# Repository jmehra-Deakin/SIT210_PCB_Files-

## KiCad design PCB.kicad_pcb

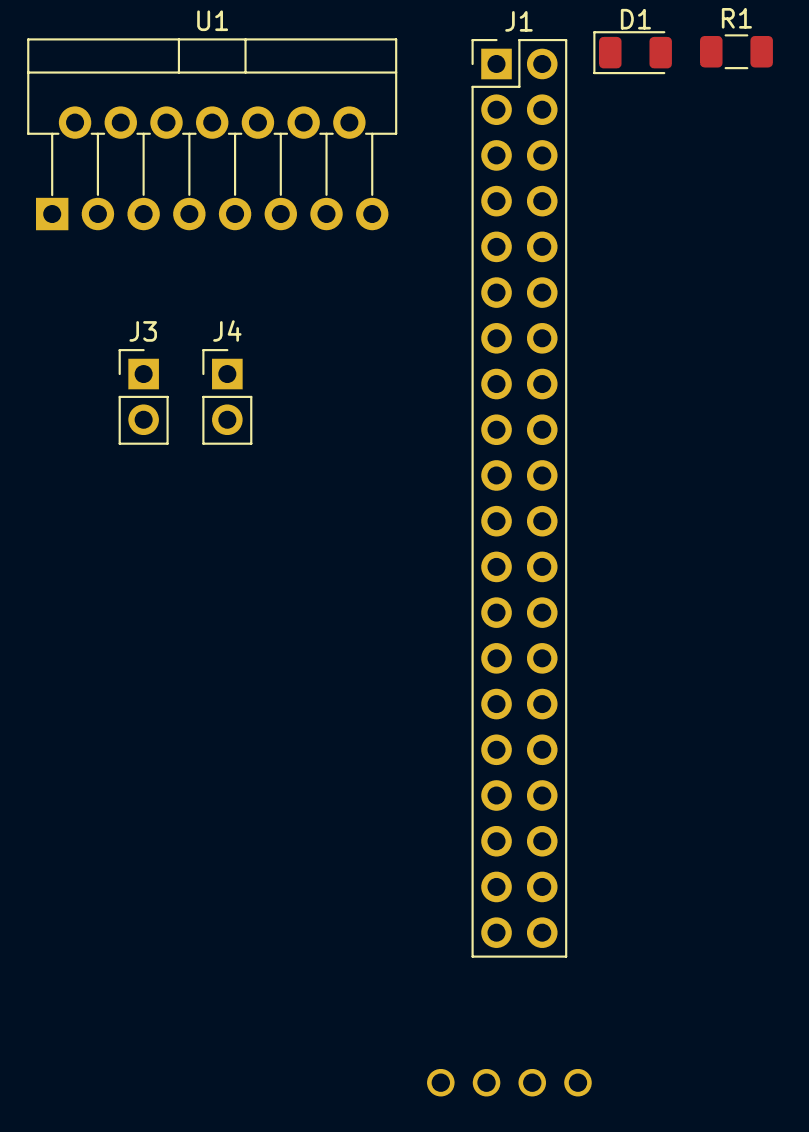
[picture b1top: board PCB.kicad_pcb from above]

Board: 2 copper layers, 7 parts (0 on the bottom side), 18 nets, no tracks yet.

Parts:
D1: LED; LED_1206_3216Metric
J1: Conn_02x20_Odd_Even; PinHeader_2x20_P2.54mm_Vertical
J3, J4: Conn_01x02_Male; PinHeader_1x02_P2.54mm_Vertical
R1: 200; R_1206_3216Metric
U1: L298HN; TO-220-15_P2.54x2.54mm_StaggerOdd_Lead4.58mm_Vertical
U2: HC-SR04; XCVR_HC-SR04

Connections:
unnamed: D1.1, R1.1
unnamed: D1.2, J1.1
unnamed: J1.2, U2.1
unnamed: J1.3, U1.5
unnamed: J1.5, U1.7
unnamed: J1.7, U1.6
unnamed: J1.12, U1.10
unnamed: J1.16, U1.12
unnamed: J1.18, U1.11
unnamed: J1.25, R1.2
unnamed: J1.30, U1.8
unnamed: J1.35, U2.3
unnamed: J1.37, U2.2
unnamed: J1.39, U2.4
unnamed: J3.1, U1.3
unnamed: J3.2, U1.2
unnamed: J4.1, U1.14
unnamed: J4.2, U1.13

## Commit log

2020-05-15 second commit
